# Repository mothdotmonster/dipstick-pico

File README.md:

# DIPSTICKpico

a smaller RP2040 board with USB-C.

[PRODUCTION FILES](https://github.com/mothdotmonster/dipstick-pico/releases/latest)

based off [RPcube](https://github.com/diminDDL/rpcube)  
uses [Paw-Connect](https://github.com/LeoDJ/Paw-Connect)

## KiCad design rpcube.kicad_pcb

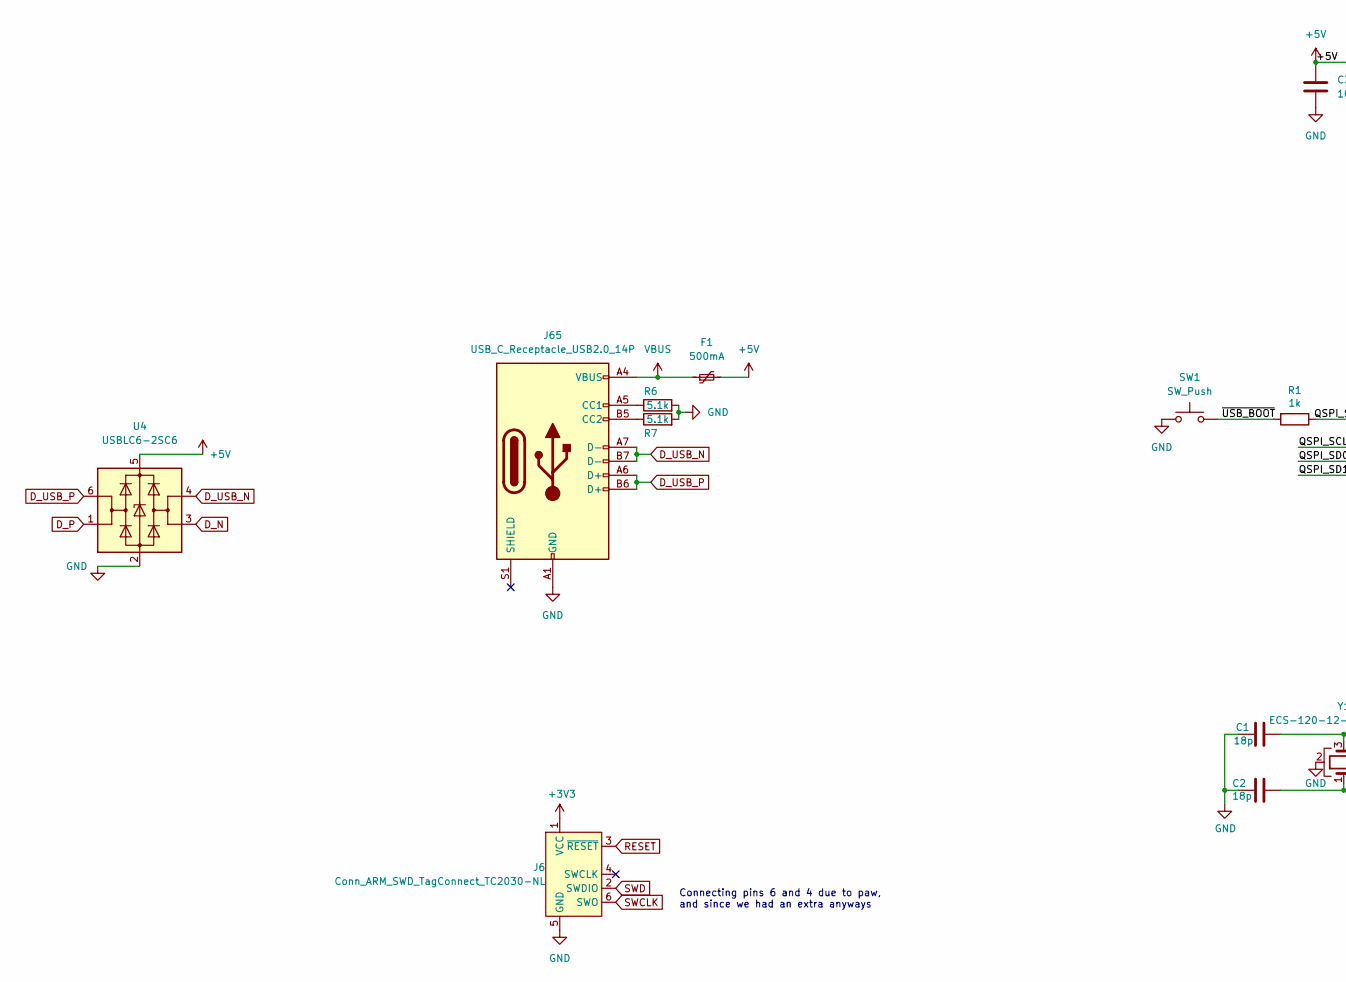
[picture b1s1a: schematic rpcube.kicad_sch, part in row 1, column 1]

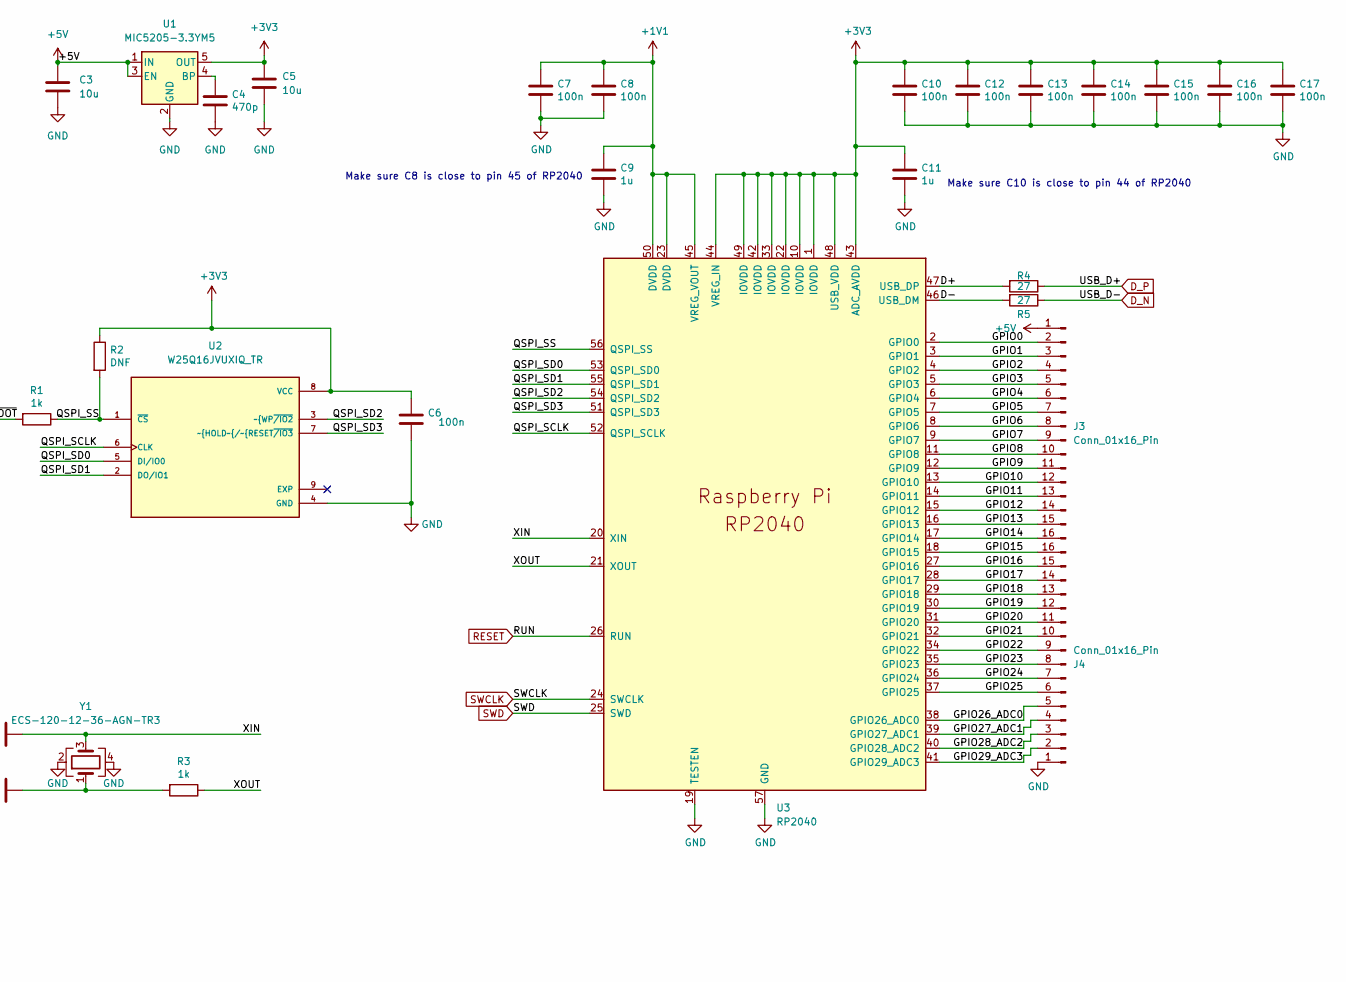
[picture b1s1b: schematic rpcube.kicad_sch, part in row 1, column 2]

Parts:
C1, C2: 18p; C_0402_1005Metric; LCSC C1549
C3: 10u; C_0603_1608Metric; LCSC C19702
C4: 470p; C_0402_1005Metric; LCSC C52923
C5: 10u; C_0402_1005Metric; LCSC C15525
C6, C7, C8, C10, C12, C13, C14, C15, C16, C17: 100n; C_0402_1005Metric; LCSC C1525
C9, C11: 1u; C_0402_1005Metric; LCSC C52923
F1: 500mA; Fuse_1206_3216Metric; LCSC C70076
J3, J4: Conn_01x16_Pin; PinHeader_1x16_P2.54mm_Vertical
J6: Conn_ARM_SWD_TagConnect_TC2030-NL; Tag-Connect_TC2030-IDC-NL_2x03_P1.27mm_Vertical
J65: USB_C_Receptacle_USB2.0_14P; USB_C_Receptacle_HRO_TYPE-C-31-M-12; LCSC C165948
R1, R3: 1k; R_0402_1005Metric; LCSC C11702
R2: DNF; R_0402_1005Metric
R4, R5: 27; R_0402_1005Metric; LCSC C25092
R6, R7: 5.1k; R_0402_1005Metric; LCSC C25905
SW1: SW_Push; SW_EVQ-P7A01P; LCSC C79167
U1: MIC5205-3.3YM5; SOT-23-5; LCSC C37970
U2: W25Q16JVUXIQ_TR; IC_W25Q16JVUXIQ_TR; PARTREV H; LCSC C2843335
U3: RP2040; RP2040-QFN-56; LCSC C2040
U4: USBLC6-2SC6; SOT-23-6; LCSC C2827654
Y1: ECS-120-12-36-AGN-TR3; Crystal_SMD_2520-4Pin_2.5x2.0mm; LCSC C479184

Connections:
+1V1: C7.1, C8.1, C9.1, U3.23 (DVDD), U3.45 (VREG_VOUT), U3.50 (DVDD)
+3V3: C5.1, C6.1, C10.1, C11.1, C12.1, C13.1, C14.1, C15.1, C16.1, C17.1, J6.1 (VCC), R2.1, U1.5 (OUT), U2.8 (VCC), U3.1 (IOVDD), U3.10 (IOVDD), U3.22 (IOVDD), U3.33 (IOVDD), U3.42 (IOVDD), U3.43 (ADC_AVDD), U3.44 (VREG_IN), U3.48 (USB_VDD), U3.49 (IOVDD)
+5V: C3.1, F1.2, J3.1, U1.1 (IN), U1.3 (EN), U4.5 (VBUS)
/D+: R4.2, U3.47 (USB_DP)
/D-: R5.2, U3.46 (USB_DM)
/GPIO0: J3.2, U3.2 (GPIO0)
/GPIO1: J3.3, U3.3 (GPIO1)
/GPIO2: J3.4, U3.4 (GPIO2)
/GPIO3: J3.5, U3.5 (GPIO3)
/GPIO4: J3.6, U3.6 (GPIO4)
/GPIO5: J3.7, U3.7 (GPIO5)
/GPIO6: J3.8, U3.8 (GPIO6)
/GPIO7: J3.9, U3.9 (GPIO7)
/GPIO8: J3.10, U3.11 (GPIO8)
/GPIO9: J3.11, U3.12 (GPIO9)
/GPIO10: J3.12, U3.13 (GPIO10)
/GPIO11: J3.13, U3.14 (GPIO11)
/GPIO12: J3.14, U3.15 (GPIO12)
/GPIO13: J3.15, U3.16 (GPIO13)
/GPIO14: J3.16, U3.17 (GPIO14)
/GPIO15: J4.16, U3.18 (GPIO15)
/GPIO16: J4.15, U3.27 (GPIO16)
/GPIO17: J4.14, U3.28 (GPIO17)
/GPIO18: J4.13, U3.29 (GPIO18)
/GPIO19: J4.12, U3.30 (GPIO19)
/GPIO20: J4.11, U3.31 (GPIO20)
/GPIO21: J4.10, U3.32 (GPIO21)
/GPIO22: J4.9, U3.34 (GPIO22)
/GPIO23: J4.8, U3.35 (GPIO23)
/GPIO24: J4.7, U3.36 (GPIO24)
/GPIO25: J4.6, U3.37 (GPIO25)
/GPIO26_ADC0: J4.5, U3.38 (GPIO26_ADC0)
/GPIO27_ADC1: J4.4, U3.39 (GPIO27_ADC1)
/GPIO28_ADC2: J4.3, U3.40 (GPIO28_ADC2)
/GPIO29_ADC3: J4.2, U3.41 (GPIO29_ADC3)
/QSPI_SCLK: U2.6 (CLK), U3.52 (QSPI_SCLK)
/QSPI_SD0: U2.5 (DI/IO0), U3.53 (QSPI_SD0)
/QSPI_SD1: U2.2 (DO/IO1), U3.55 (QSPI_SD1)
/QSPI_SD2: U2.3 (~WP~{/IO2), U3.54 (QSPI_SD2)
/QSPI_SD3: U2.7 (~HOLD~{/~{RESET~{/IO3), U3.51 (QSPI_SD3)
/QSPI_SS: R1.1, R2.2, U2.1 (~CS), U3.56 (QSPI_SS)
/XIN: C1.1, U3.20 (XIN), Y1.3
/XOUT: R3.1, U3.21 (XOUT)
/~USB_BOOT: R1.2, SW1.1_1, SW1.2
D_N: R5.1, U4.3 (I/O2)
D_P: R4.1, U4.1 (I/O1)
D_USB_N: J65.A7 (D-), J65.B7 (D-), U4.4 (I/O2)
D_USB_P: J65.A6 (D+), J65.B6 (D+), U4.6 (I/O1)
GND: C1.2, C2.2, C3.2, C4.2, C5.2, C6.2, C7.2, C8.2, C9.2, C10.2, C11.2, C12.2, C13.2, C14.2, C15.2, C16.2, C17.2, J4.1, J6.5 (GND), J65.A1 (GND), J65.A12 (GND), J65.B1 (GND), J65.B12 (GND), R6.2, R7.2, SW1.1, SW1.2_1, SW1.2_2, U1.2 (GND), U2.4 (GND), U3.19 (TESTEN), U3.57 (GND), U4.2 (GND), Y1.2, Y1.4
unnamed: C2.1, R3.2, Y1.1
unnamed: J65.A5 (CC1), R6.1
unnamed: J65.B5 (CC2), R7.1
unnamed: C4.1, U1.4 (BP)
RESET: J6.3 (~RESET), U3.26 (RUN)
SWCLK: J6.6 (SWO), U3.24 (SWCLK)
SWD: J6.2 (SWDIO), U3.25 (SWD)
VBUS: F1.1, J65.A4 (VBUS), J65.A9 (VBUS), J65.B4 (VBUS), J65.B9 (VBUS)

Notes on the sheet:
Make sure C10 is close to pin 44 of RP2040
Connecting pins 6 and 4 due to paw, and since we had an extra anyways
Make sure C8 is close to pin 45 of RP2040

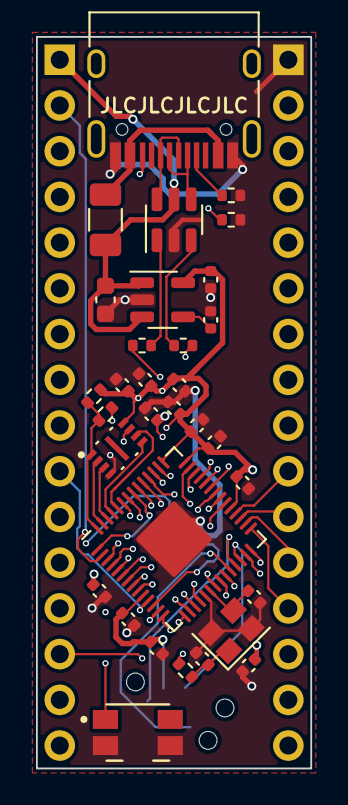
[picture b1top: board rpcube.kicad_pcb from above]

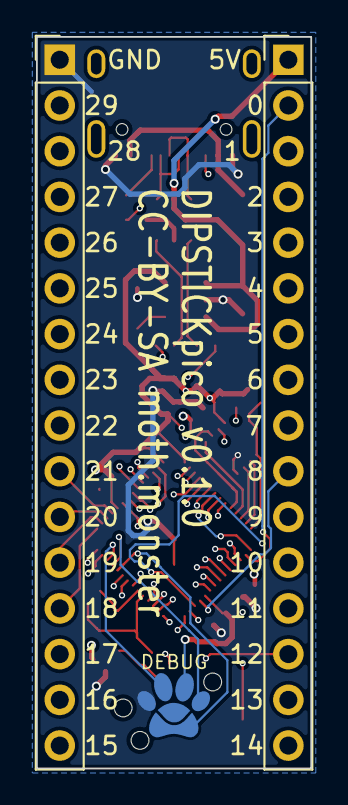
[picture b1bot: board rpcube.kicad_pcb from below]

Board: 4 copper layers, 15.2 x 40.6 mm, 35 parts (3 on the bottom side), 57 nets.

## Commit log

2024-07-29 add readme and stuff
2024-07-29 forgot to rename those somehow
2024-07-29 add license

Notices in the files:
rpcube.kicad_pcb:
CC-BY-SA moth.monster
